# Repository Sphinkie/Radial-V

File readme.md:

# Radial-V

## Présentation

Remise en fonctionnement d'un poste de TSF, avec radio FM, player MP3, et afficheur LCD.

## Fabrication

Plusieurs éléments ont été réalisés: logiciel, circuits électroniques et supports en PLA.

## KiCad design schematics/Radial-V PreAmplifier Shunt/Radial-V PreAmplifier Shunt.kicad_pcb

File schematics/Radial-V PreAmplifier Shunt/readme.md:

# Radial-V

## Mini-Carte "PreAmplifier Shunt"

Le préamplificateur initialement prévu s'est avéré inutile: le signal en sortie de l'ampli étant alors trop puissant. Le préamplificateur a donc été remplacé par cette mini-carte de *shunt*.

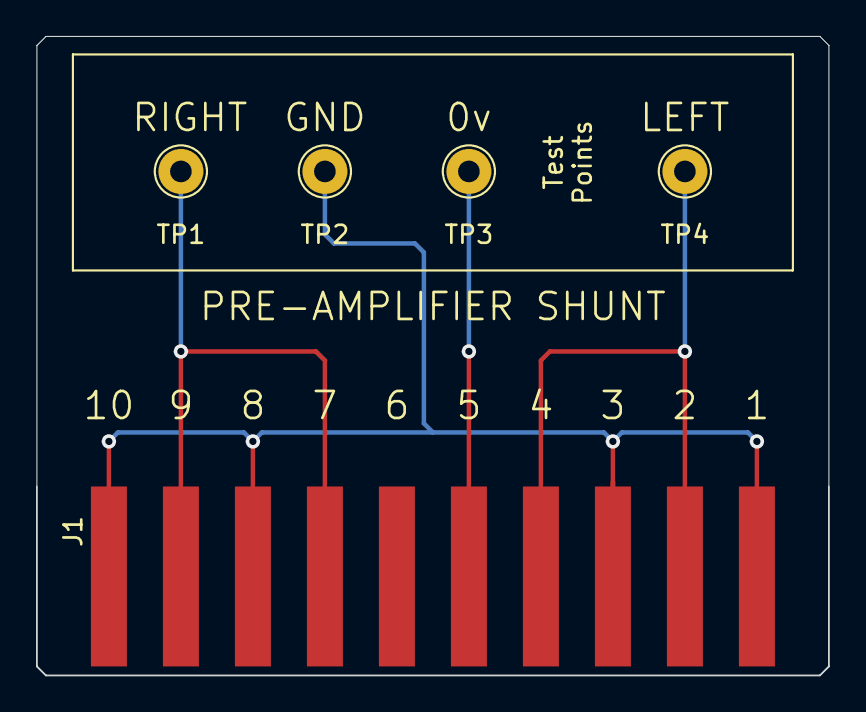
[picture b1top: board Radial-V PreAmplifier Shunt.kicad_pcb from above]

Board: 2 copper layers, 44.0 x 35.5 mm, 5 parts (0 on the bottom side), 4 nets.

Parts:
J1: Edge Connector 1x10; PCB_Edge_1x10
TP1, TP2, TP3, TP4: TestPoint; TestPoint_THTPad_D2.5mm_Drill1.2mm

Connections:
/0v: J1.5, TP3.1
/AudioLeft: J1.2, J1.4, TP4.1
/AudioRight: J1.7, J1.9, TP1.1
GND: J1.1, J1.3, J1.8, J1.10, TP2.1

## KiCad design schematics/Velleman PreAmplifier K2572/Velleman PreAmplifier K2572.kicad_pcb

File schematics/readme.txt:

To generate the file for JLB PCB:

kiCad → Pcbnew → File → Plot...
  Plot format: Gerber
  Output directory: Gerber\
  Included layers: F.Cu B.Cu F.SilkS B.SilkS F.Mask B.Mask Edge.Cuts
  Plot footprint values
  Plot footprint references
  Exclude PDB edge layer from other layers
  Exclude pads from silkscreen

Plot

Generate Drill Files...
Generate Drill Files

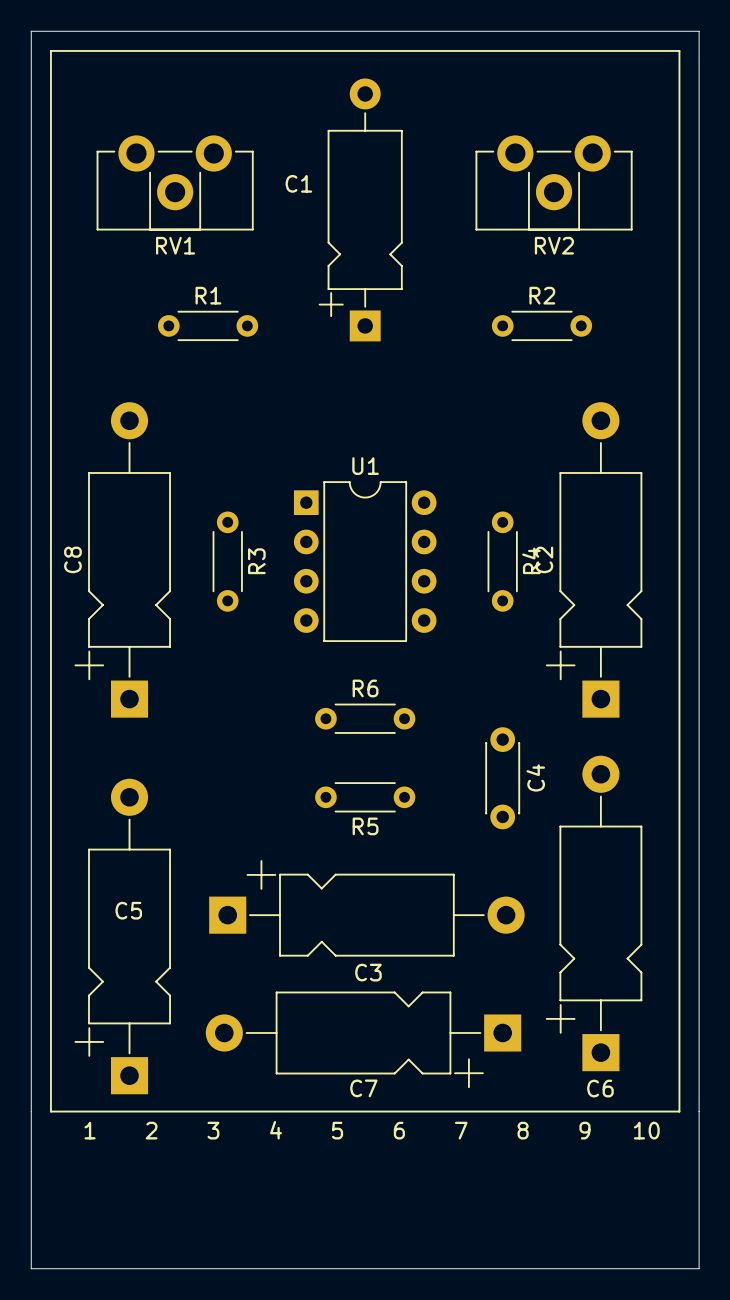
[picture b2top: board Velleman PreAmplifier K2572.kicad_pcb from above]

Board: 2 copper layers, 43.2 x 80.0 mm, 18 parts (1 on the bottom side), 15 nets, no tracks yet.

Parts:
C1: 10u; CP_Axial_L10.0mm_D4.5mm_P15.00mm_Horizontal
C2, C3, C5, C6, C7, C8: 1u; CP_Axial_L11.0mm_D5.0mm_P18.00mm_Horizontal
C4: 100n; C_Disc_D4.3mm_W1.9mm_P5.00mm
J1: Conn_01x10; Hirose_DF3EA-10P-2H_1x10-1MP_P2.00mm_Horizontal
R1, R2: 22k; R_Axial_DIN0204_L3.6mm_D1.6mm_P5.08mm_Horizontal
R3, R4: 1M; R_Axial_DIN0204_L3.6mm_D1.6mm_P5.08mm_Horizontal
R5, R6: 10k; R_Axial_DIN0204_L3.6mm_D1.6mm_P5.08mm_Horizontal
RV1, RV2: R_POT; Potentiometer_ACP_CA9-H2,5_Horizontal
U1: TL072; DIP-8_W7.62mm

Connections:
/IN-L: C7.2, J1.4
/IN-R: C6.2, J1.7
/OUT-L: C8.1, J1.2
/OUT-R: C5.1, J1.9
GNDD: C1.2, C4.2, J1.1, J1.3, J1.5, J1.8, J1.10, R1.2, RV1.3, RV2.3, U1.4
unnamed: C1.1, C6.1, C7.1, R1.1, R2.2, R5.2, R6.2, U1.2, U1.6
unnamed: C2.1, R3.1, U1.1
unnamed: C2.2, RV1.1
unnamed: C3.1, R4.1, U1.7
unnamed: C3.2, RV2.1
unnamed: C5.2, RV2.2
unnamed: C8.2, RV1.2
unnamed: R3.2, R6.1, U1.3
unnamed: R4.2, R5.1, U1.5
VCC: C4.1, J1.6, R2.1, U1.8

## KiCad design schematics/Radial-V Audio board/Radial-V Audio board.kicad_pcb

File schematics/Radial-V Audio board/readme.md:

# Radial-V

## Carte "Audio-Board"

Cette carte fait passer la sortie audio (en provenance de la carte "Extension Bus") par un Pré-Amplificateur, le potentiomètre de volume, et un Amplificateur mono. Le haut-parleur (4 ou 8 ohms) peut être branché directement sur "Audio OUT".

### Schéma d'implémentation

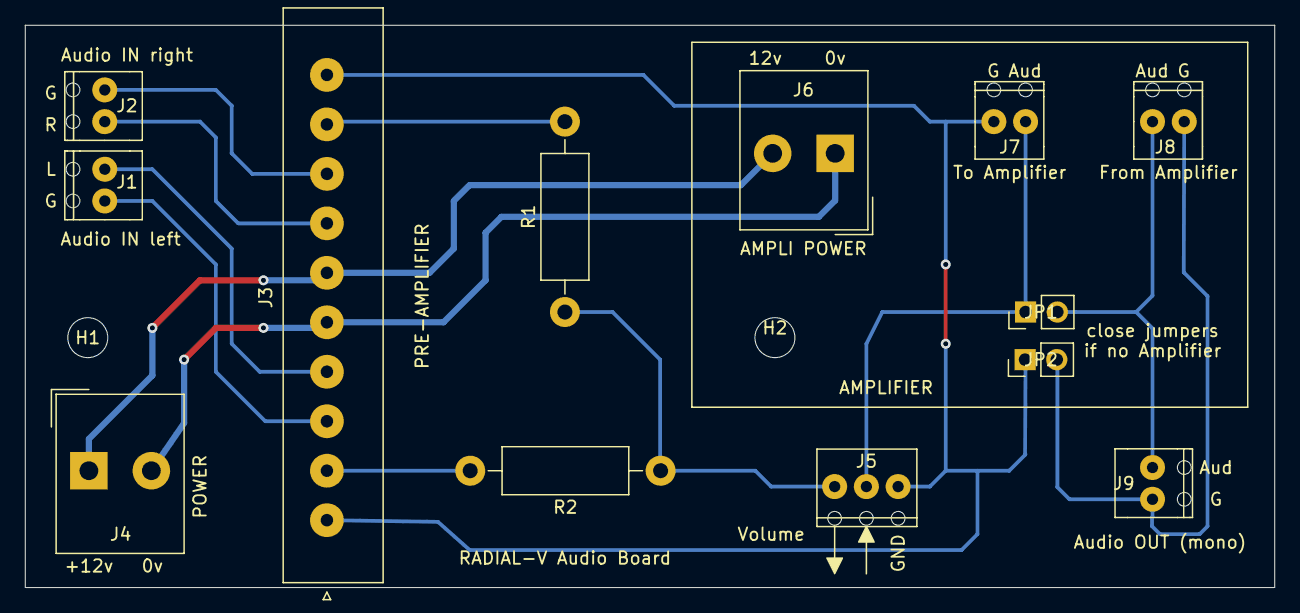
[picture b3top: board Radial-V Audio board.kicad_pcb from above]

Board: 2 copper layers, 100.0 x 45.0 mm, 15 parts (0 on the bottom side), 13 nets.

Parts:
H1, H2: MountingHole; MountingHole_3.2mm_M3
J1: Audio IN left; Bloc_de_jonction_CI-MPT_2.54mm_01x02
J2: Audio IN right; Bloc_de_jonction_CI-MPT_2.54mm_01x02
J3: Slot PreAmplifier; Edge_Connector_10P_1x10_P3.96mm_Vertical
J4: Power Supply; Altech_AK300_1x02_P5.00mm_45-Degree
J5: Volume; Bloc_de_jonction_CI-MPT_2.54mm_01x03
J6: Alim Ampli; Altech_AK300_1x02_P5.00mm_45-Degree
J7: To Amplifier; Bloc_de_jonction_CI-MPT_2.54mm_01x02
J8: From Amplifier; Bloc_de_jonction_CI-MPT_2.54mm_01x02
J9: Audio OUT (mono); Bloc_de_jonction_CI-MPT_2.54mm_01x02
JP1, JP2: Jumper_NO; PinHeader_1x02_P2.54mm_Vertical
R1, R2: 10k; R_Axial_DIN0411_L9.9mm_D3.6mm_P15.24mm_Horizontal

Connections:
/GND: J3.5, J4.2, J6.1
/GND_IN_L: J1.1, J3.3
/GND_IN_R: J2.2, J3.8
/GND_MONO: J3.1, J3.10, J5.1, J7.1, JP2.1
/GND_OUT: J8.2, J9.2, JP2.2
/IN_LEFT: J1.2, J3.4
/IN_RIGHT: J2.1, J3.7
/MONO: J5.3, R1.1, R2.1
/MONO_OUT: J8.1, J9.1, JP1.2
/OUT_LEFT: J3.2, R2.2
/OUT_RIGHT: J3.9, R1.2
/VDD: J3.6, J4.1, J6.2
unnamed: J5.2, J7.2, JP1.1

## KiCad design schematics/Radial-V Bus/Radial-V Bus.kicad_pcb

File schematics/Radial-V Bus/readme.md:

# Radial-V

## Carte "Bus-Board"

Cette carte rassemble toutes les pins d'entrées/sorties utilisées de l'Arduino, vers une nappe 25 points, qui conduit à la carte "Extension Board". On plugge aussi dessus la carte "Sparkfun MP3 player".

### Schéma d'implémentation

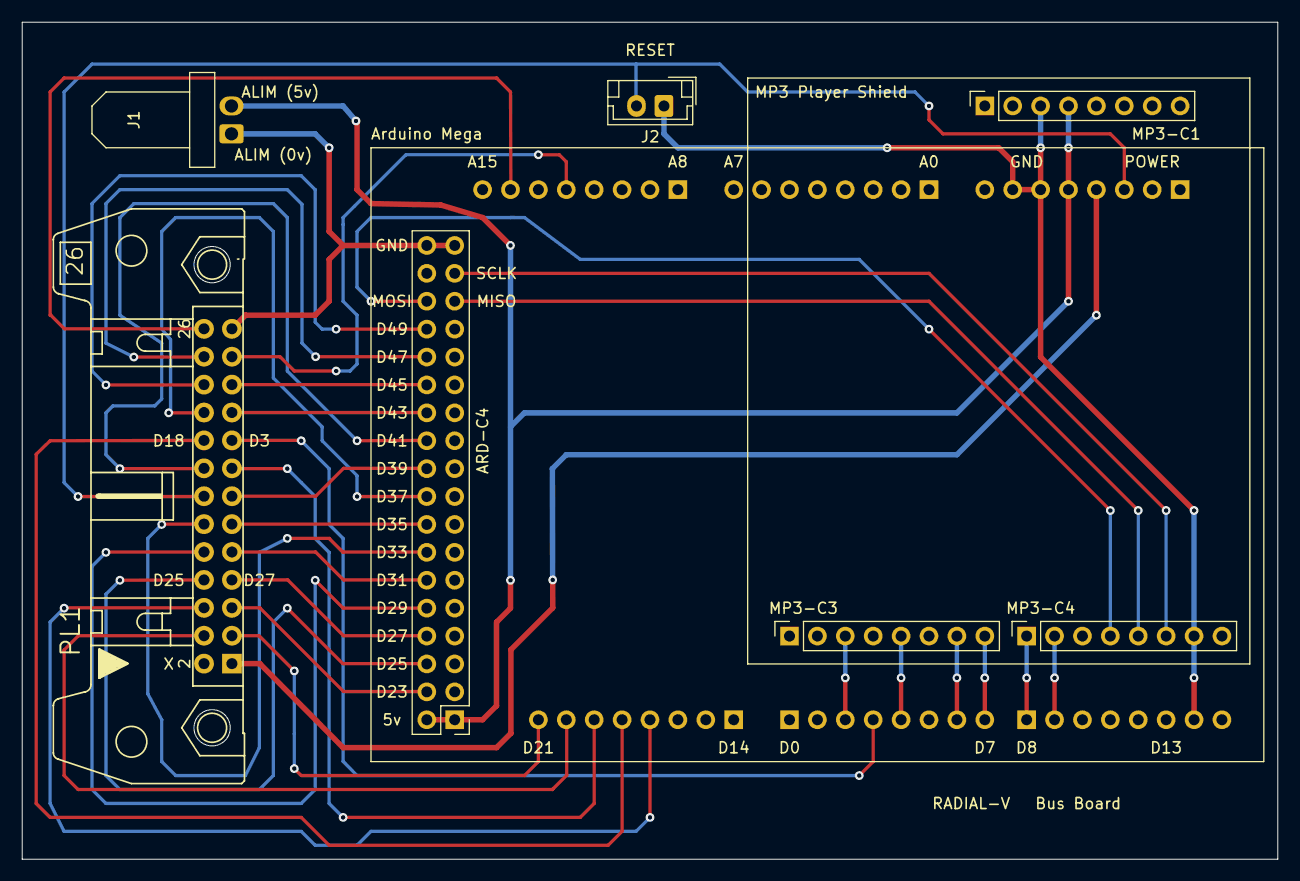
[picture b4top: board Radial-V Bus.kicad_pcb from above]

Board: 2 copper layers, 114.3 x 76.2 mm, 13 parts (0 on the bottom side), 36 nets.

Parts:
ARD-C1: POWER; PinHeader_1x08_P2.54mm_Vertical
ARD-C2: A7-A0; PinHeader_1x08_P2.54mm_Vertical
ARD-C3: A15-A8; PinHeader_1x08_P2.54mm_Vertical
ARD-C4: D22-D53; PinHeader_2x18_P2.54mm_Vertical
ARD-C5: D21-D14; PinHeader_1x08_P2.54mm_Vertical
ARD-C6: D0-D7; PinHeader_1x08_P2.54mm_Vertical
ARD-C7: D8-D13; PinHeader_1x08_P2.54mm_Vertical
J1: Conn_Alim; Molex_KK-254_AE-6410-02A_1x02_P2.54mm_Horizontal
J2: Conn_Reset; JST_EH_B2B-EH-A_1x02_P2.50mm_Vertical
MP3-C1: POWER; PinSocket_1x08_P2.54mm_Vertical
MP3-C3: I/O; PinSocket_1x08_P2.54mm_Vertical
MP3-C4: COMMS; PinSocket_1x08_P2.54mm_Vertical
PL1: Nappe; HE10-26P

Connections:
/3V3: ARD-C1.4, PL1.1
/5V: ARD-C1.5, ARD-C4.1, ARD-C4.2, J1.2, MP3-C1.4
/A12: ARD-C3.5, PL1.23
/A14: ARD-C3.7, PL1.26
/D3: ARD-C6.4, PL1.17
/D17: ARD-C5.4, PL1.6
/D18: ARD-C5.5, PL1.18
/D19: ARD-C5.6, PL1.15
/D23: ARD-C4.4, PL1.5
/D25: ARD-C4.6, PL1.8
/D27: ARD-C4.8, PL1.7
/D29: ARD-C4.10, PL1.10
/D31: ARD-C4.12, PL1.9
/D33: ARD-C4.14, PL1.12
/D35: ARD-C4.16, PL1.11
/D37: ARD-C4.18, PL1.20
/D39: ARD-C4.20, PL1.13
/D41: ARD-C4.22, PL1.16
/D43: ARD-C4.24, PL1.19
/D45: ARD-C4.26, PL1.21
/D47: ARD-C4.28, PL1.24
/D49: ARD-C4.30, PL1.22
/D50-MISO: ARD-C4.31, MP3-C4.5
/D51-MOSI: ARD-C4.32, MP3-C4.4
/D52-SCLK: ARD-C4.33, MP3-C4.6
/GND: ARD-C1.6, ARD-C1.7, ARD-C7.7, J2.1, MP3-C1.3, MP3-C4.7
/GND-ARD: ARD-C4.35, ARD-C4.36, J1.1, PL1.25
/GPIO1: ARD-C6.5, MP3-C3.5
/MP3-CS: ARD-C6.7, MP3-C3.7
/MP3-DCS: ARD-C6.8, MP3-C3.8
/MP3-DREQ: ARD-C6.3, MP3-C3.3
/SCL: ARD-C5.8, PL1.3
/SDA: ARD-C5.7, PL1.4
unnamed: ARD-C7.1, MP3-C4.1
unnamed: ARD-C7.2, MP3-C4.2
RESET: ARD-C1.3, J2.2, PL1.14

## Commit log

2018-01-25 :tada: Added .gitattributes
2018-01-25 schematics
2019-12-28 3D view des cartes
2019-12-29 Add docs for Spackfun FM card
2019-12-30 Wait for I2C Slave + Unicode converter
2019-12-31 Gestion des accents
2020-01-01 Recabling C-MODE connector
2020-01-01 Title on 2 lines
2020-01-02 Changement de de cablage
2020-01-02 Gestion du titre déroulant
2020-01-11 Affichage du Mode en rouge
2020-01-11 Adding STL files (3D printed objects)
2020-01-11 3D objects updated
2020-01-12 Meilleur rafraichissement du Rating affiché
2020-01-12 no backlight for FM
2020-01-19 Implémentation de la library pour shield FM Si7403
2020-01-20 Bus board recreated with Kicad
2020-01-21 Update Bus Board
2020-01-21 Routage Bus Board
2020-01-22 Bus Board
2020-01-26 Ajout de Radio Board
2020-01-26 wire fix
2020-01-26 Regroupement de A12 et A14 sur le même connecteur
2020-01-26 Header ARD-J4 mis sur la couche Bottom
2020-01-26 Mise à jour du mapping des I/O dans Extension Board
2020-01-26 Generation des fichiers Gerber
2020-01-26 Add readme
2020-01-26 change filenames
2020-01-26 Add a Readme for Bus Board
2020-01-26 Arduino LCD screen documentation
2020-01-28 Actualisation de documentation
2020-01-29 Mise à jour des Readme
2020-01-30 mise à jour des images
2020-02-01 change case of directory
2020-02-01 Ajout de nouvelles images
2020-02-05 3D models added
2020-02-06 Update Audio Board
2020-02-07 Add PreAmplifier Board
2020-02-07 Add Amplfier board
2020-02-09 Velleman Amplifier Board
2020-02-09 STL models added
2020-02-09 STL model added
2020-02-09 Adding preamplifier 3D model
2020-02-16 Audio support 3D model
2020-02-16 fichiers remis dans le bon repertoire...
2020-02-20 Updated models
2020-02-23 Remmaping des E/S après installation BusBoard V2
2020-02-23 Essai de vérification si Arduino Slave present
    Peut être utile car la librarie WIRE se bloque s'il n'y a pas de Slave I2C.
2020-02-24 Aout de la possibilité de tester avec Arduino 2 deconnecté
2020-03-02 Calibrage de la Capa Variable (in progress)
2020-03-04 Mersure de la Capa
    par une meilleure méthode
2020-03-05 Etalonnage des mesures de la capa
2020-03-06 Mesure stabilisée de la capa : OK
2020-03-07 cleanup code
2020-03-09 updated component view
2020-03-09 Updated picture size
2020-03-10 Fichier readme
2020-03-10 readme
2020-03-23 with comments
2020-03-24 documentation
2020-04-10 Include Si4703 FM shield library
2020-04-10 Testing FM player (wip)
2020-04-10 There are I2C NACK errors
2020-04-13 Le code pour la FM est en place: masi ABANDON
    Abandon de la foncrtionnalité FM, car impossible de communiquer avec la carte Si4703.
    La librairie reste en place, ainsi de futures tentatives restent possibles...
2020-04-16 Tests unitaires de la carte FM.
    NACK si on met des adaptations de tension.
    OK si on ne met aucune adaptation...
    génial....
2020-04-16 Adjust Si4703 demo
2020-04-18 VERSION 2.3 - ABANDON DE LA FM
2020-04-20 Adding Amplifier Shunt board
2020-05-01 Classe de base CatalogFile
2020-05-01 Nouvelle classe MEDIA
2020-05-01 Reorganisation de la recherche (WIP)
2020-05-02 Reorganisation de la recherche (Done)
2020-05-09 New Catalog
2020-05-10 screenshots
2020-05-11 Patches pour VLSI
2020-05-16 Ajout des mini-cartes "Audio Adapter" et "Capa Adapter" et "PreAmp Shunt"
2020-05-17 Cleanup 3D models
2020-05-17 updated readme.md and pictures
2020-05-19 renommage de l'objet
2020-05-20 Pictures
2020-05-25 Détails du fichier Catalog
2020-08-01 update des tools
2020-10-15 Directory change
2020-10-15 Github web pages
2020-10-15 web pages
2020-10-15 Transparency
2022-03-31 update documentation
2022-04-03 Ajout KiCad Library: MesModules
2022-05-01 Project Githup Page
2022-05-02 détourage photos
2022-05-03 photo reworked
2024-02-11 Images et photos
    Détourage
2025-03-24 remove background
